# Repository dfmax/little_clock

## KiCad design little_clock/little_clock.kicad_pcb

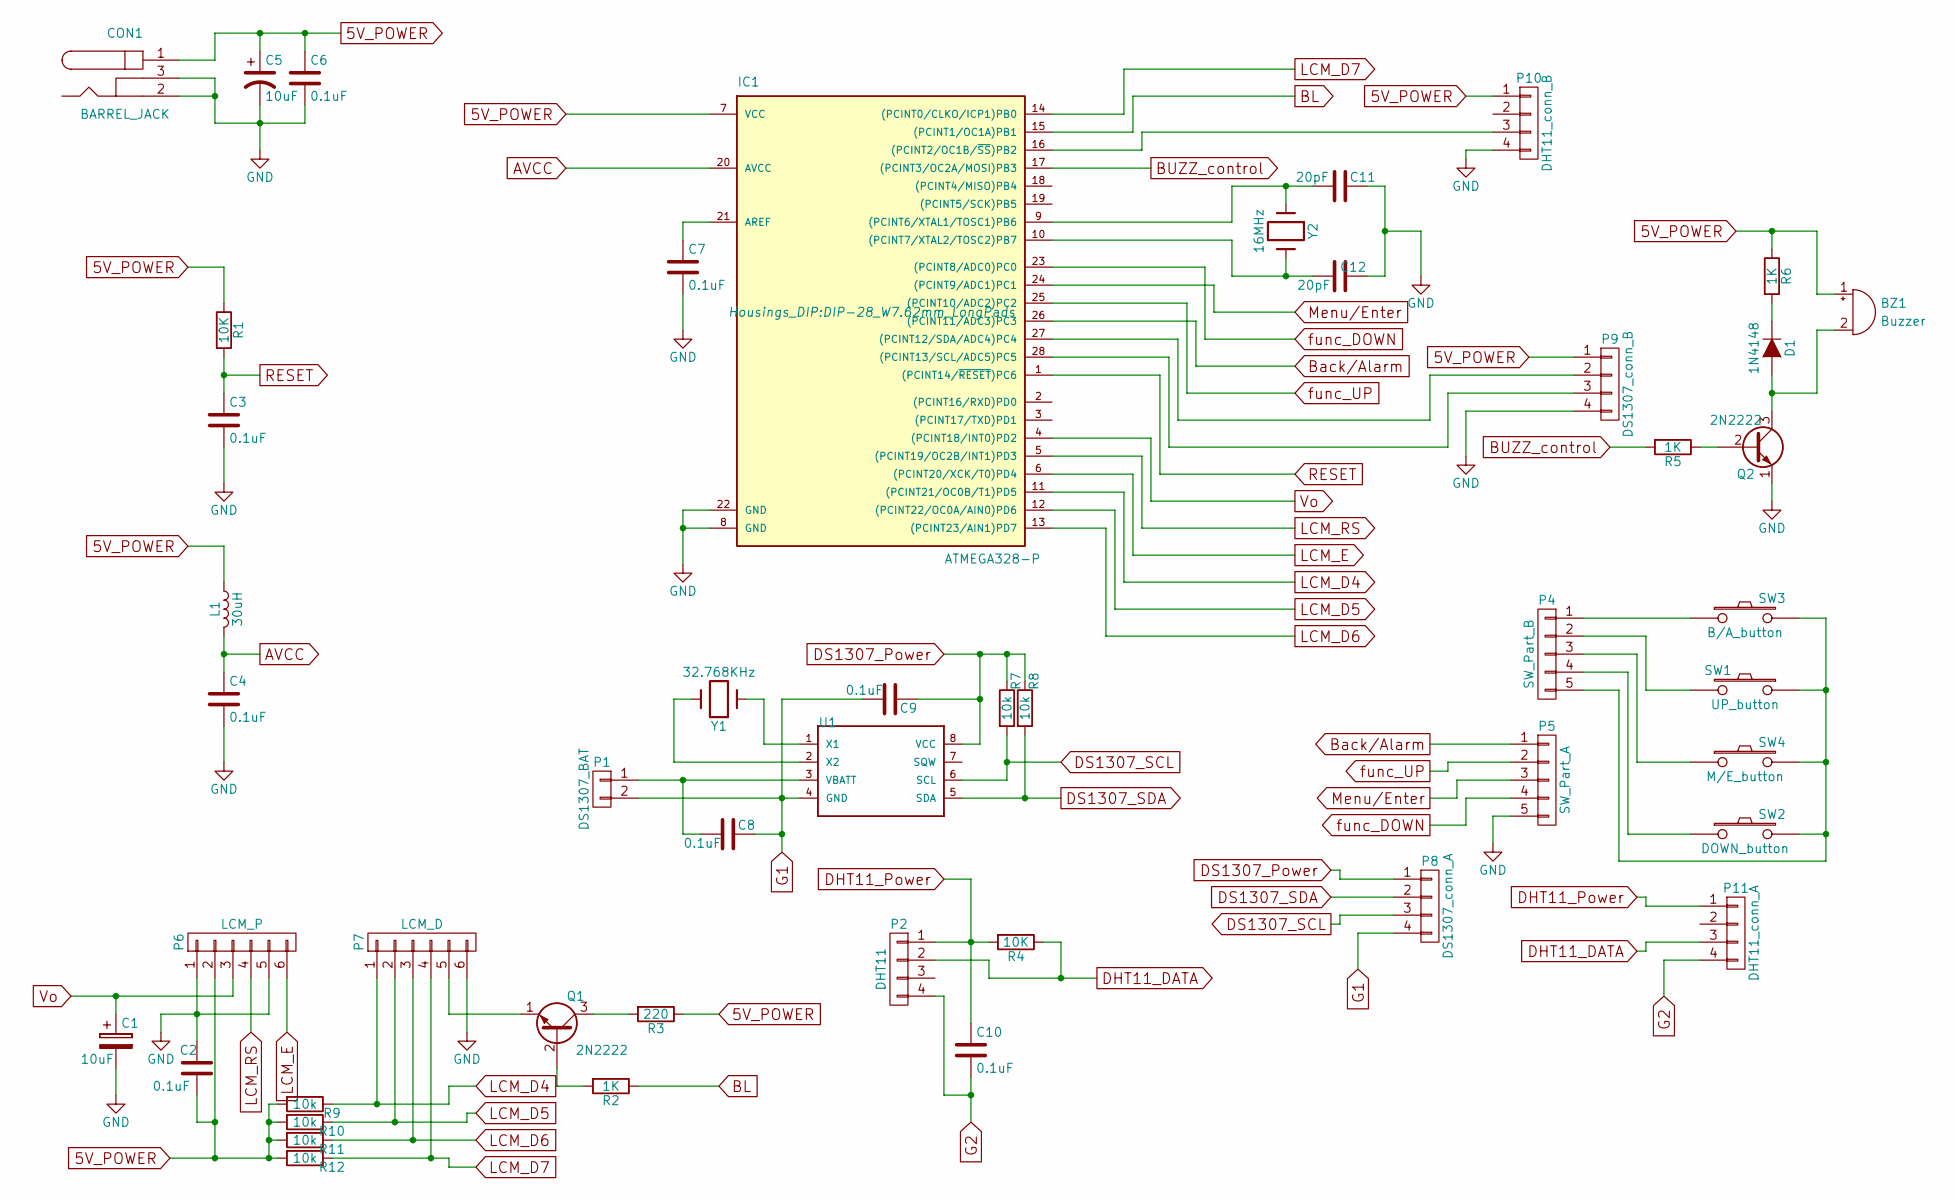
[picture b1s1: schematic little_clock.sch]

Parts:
BZ1: Buzzer; Buzzer_12x9.5RM7.6
C1, C5: 10uF; CP_Radial_D5.0mm_P2.50mm
C2, C6, C7, C8, C9, C10: 0.1uF; C_Disc_D5.0mm_W2.5mm_P5.00mm
C3, C4: 0.1uF; C_Disc_D4.7mm_W2.5mm_P5.00mm
C11, C12: 20pF; C_Disc_D3.0mm_W1.6mm_P2.50mm
CON1: BARREL_JACK
D1: 1N4148; D_DO-41_SOD81_P7.62mm_Horizontal
IC1: ATMEGA328-P; DIP-28_W7.62mm_LongPads
L1: 30uH; R_Axial_DIN0207_L6.3mm_D2.5mm_P10.16mm_Horizontal
P1: DS1307_BAT; Socket_Strip_Straight_2x01_Pitch2.54mm
P2: DHT11; Molex_NanoFit_1x04x2.50mm_Angled
P4: SW_Part_B; Pin_Header_Straight_1x05_Pitch2.54mm
P5: SW_Part_A; Pin_Header_Straight_1x05_Pitch2.54mm
P6: LCM_P; Pin_Header_Straight_1x06_Pitch2.54mm
P7: LCM_D; Pin_Header_Straight_1x06_Pitch2.54mm
P8: DS1307_conn_A; Pin_Header_Straight_1x04_Pitch2.54mm
P9: DS1307_conn_B; Pin_Header_Straight_1x04_Pitch2.54mm
P10: DHT11_conn_B; Pin_Header_Straight_1x04_Pitch2.54mm
P11: DHT11_conn_A; Pin_Header_Straight_1x04_Pitch2.54mm
Q1, Q2: 2N2222; TO-92_Inline_Wide
R1, R4: 10K; R_Axial_DIN0207_L6.3mm_D2.5mm_P10.16mm_Horizontal
R2, R5, R6: 1K; R_Axial_DIN0207_L6.3mm_D2.5mm_P10.16mm_Horizontal
R3: 220; R_Axial_DIN0207_L6.3mm_D2.5mm_P10.16mm_Horizontal
R7, R8, R9, R10, R11, R12: 10k; R_Axial_DIN0207_L6.3mm_D2.5mm_P10.16mm_Horizontal
SW1: UP_button; SW_PUSH_SMALL
SW2: DOWN_button; SW_PUSH_SMALL
SW3: B/A_button; SW_PUSH_SMALL
SW4: M/E_button; SW_PUSH_SMALL
U1: DS1307; DIP-8_W7.62mm_Socket_LongPads
Y1: 32.768KHz; Crystal_AT310_d3.0mm_l10.0mm_Horizontal
Y2: 16MHz; Crystal_HC18-U_Vertical

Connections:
5V_POWER: BZ1.1 (-), C2.2, C5.1, C6.1, CON1.1, IC1.7 (VCC), L1.1, P6.2, P9.1, P10.1, R1.1, R3.1, R6.1, R9.2, R10.2, R11.2, R12.2
AVCC: C4.1, IC1.20 (AVCC), L1.2
BL: IC1.15 ((PCINT1/OC1A)PB1), R2.1
BUZZ_control: IC1.17 ((PCINT3/OC2A/MOSI)PB3), R5.2
Back/Alarm: IC1.26 ((PCINT11/ADC3)PC3), P5.1
DHT11_DATA: P2.2, P11.3, R4.1
DHT11_Power: C10.1, P2.1, P11.1, R4.2
DS1307_Power: C9.1, P8.1, R7.1, R8.1, U1.8 (VCC)
DS1307_SCL: P8.3, R7.2, U1.6 (SCL)
DS1307_SDA: P8.2, R8.2, U1.5 (SDA)
G1: C8.1, C9.2, P1.2, P8.4, U1.4 (GND)
G2: C10.2, P2.4, P11.4
GND: C1.2, C2.1, C3.2, C4.2, C5.2, C6.2, C7.2, C11.1, C12.2, CON1.2, CON1.3, IC1.8 (GND), IC1.22 (GND), P5.5, P6.1, P6.5, P7.6, P9.4, P10.4, Q2.1 (E)
LCM_D4: IC1.11 ((PCINT21/OC0B/T1)PD5), P7.1, R9.1
LCM_D5: IC1.12 ((PCINT22/OC0A/AIN0)PD6), P7.2, R10.1
LCM_D6: IC1.13 ((PCINT23/AIN1)PD7), P7.3, R11.1
LCM_D7: IC1.14 ((PCINT0/CLKO/ICP1)PB0), P7.4, R12.1
LCM_E: IC1.6 ((PCINT20/XCK/T0)PD4), P6.6
LCM_RS: IC1.5 ((PCINT19/OC2B/INT1)PD3), P6.4
Menu/Enter: IC1.24 ((PCINT9/ADC1)PC1), P5.3
unnamed: BZ1.2 (+), D1.2 (A), Q2.3 (C)
unnamed: C7.1, IC1.21 (AREF)
unnamed: C8.2, P1.1, U1.3 (VBATT)
unnamed: C11.2, IC1.9 ((PCINT6/XTAL1/TOSC1)PB6), Y2.1
unnamed: C12.1, IC1.10 ((PCINT7/XTAL2/TOSC2)PB7), Y2.2
unnamed: D1.1 (K), R6.2
unnamed: IC1.16 ((PCINT2/OC1B/~SS~)PB2), P10.3
unnamed: IC1.27 ((PCINT12/SDA/ADC4)PC4), P9.2
unnamed: IC1.28 ((PCINT13/SCL/ADC5)PC5), P9.3
unnamed: P4.1, SW3.1
unnamed: P4.2, SW1.2
unnamed: P4.3, SW4.1
unnamed: P4.4, SW2.1
unnamed: P4.5, SW1.1, SW2.2, SW3.2, SW4.2
unnamed: P7.5, Q1.1 (E)
unnamed: Q1.2 (B), R2.2
unnamed: Q1.3 (C), R3.2
unnamed: Q2.2 (B), R5.1
unnamed: U1.1 (X1), Y1.1
unnamed: U1.2 (X2), Y1.2
RESET: C3.1, IC1.1 ((PCINT14/~RESET~)PC6), R1.2
Vo: C1.1, IC1.4 ((PCINT18/INT0)PD2), P6.3
func_DOWN: IC1.23 ((PCINT8/ADC0)PC0), P5.4
func_UP: IC1.25 ((PCINT10/ADC2)PC2), P5.2

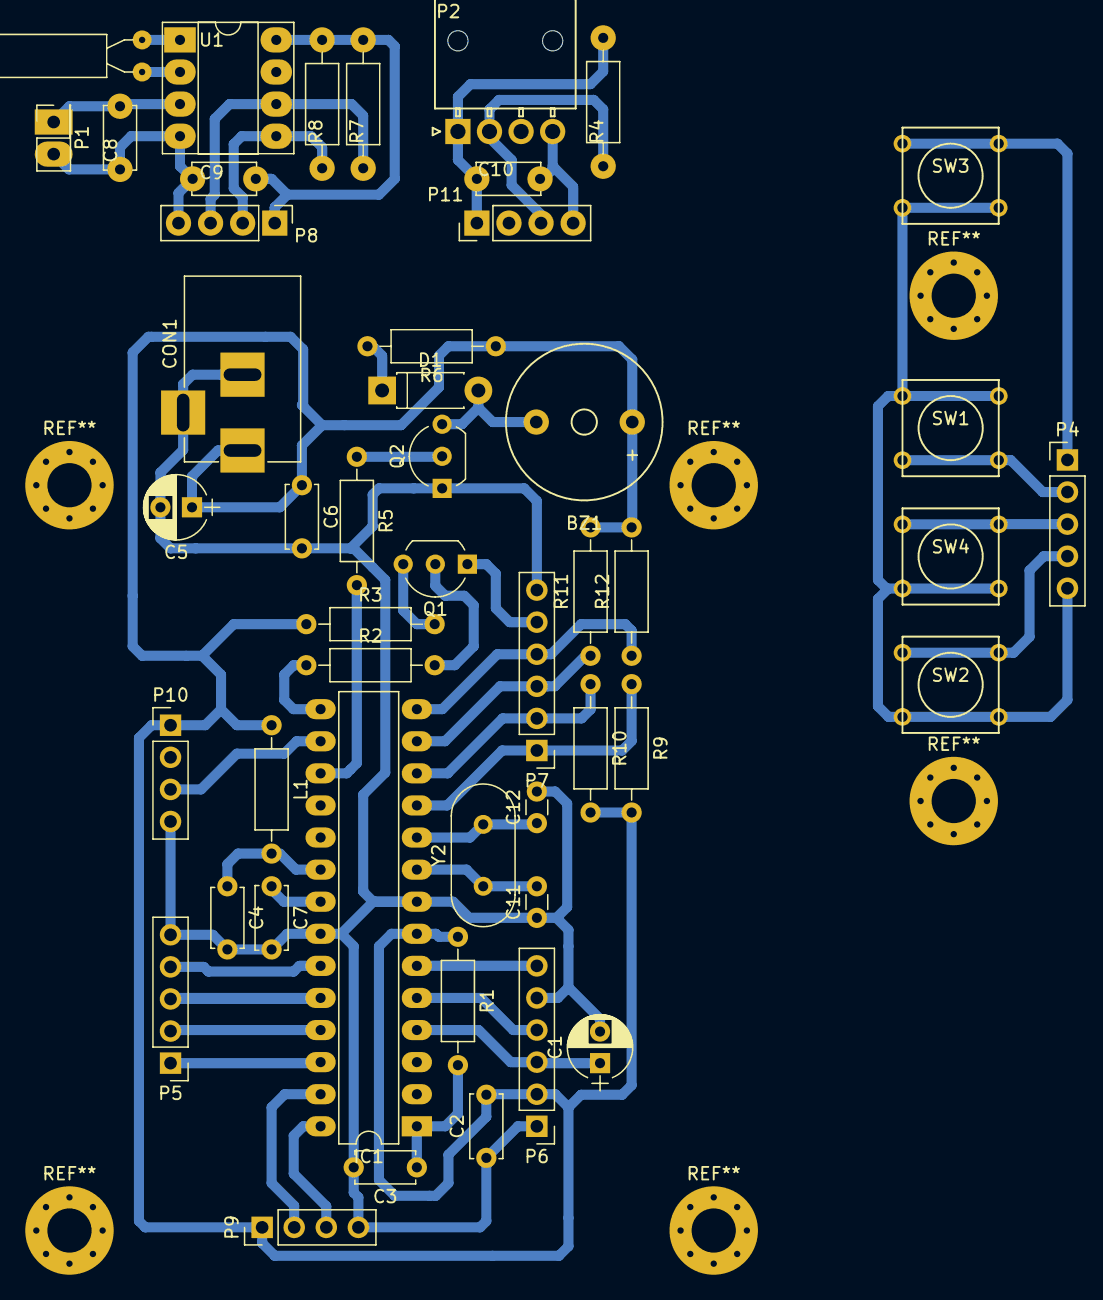
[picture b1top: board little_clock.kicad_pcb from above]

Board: 2 copper layers, 48 parts (0 on the bottom side), 44 nets.

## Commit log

2017-01-17 Basic functions for arduino digital clock
    functions by now:
    1. show time、date、temperature.
    2. autosave RTC time to eeprom.
    3. read RTC time.
    4. can using process code to control backlight and contrast.
2017-01-18 add some define, and fix initial display bug.
    add:
    1. add read LM35 data limit function.
    2. define control SW.
    3. setting show temperature limit to 99 degrees Celsius.
    edit:
    1. edit LM35 read delay time.
2017-01-19 add setting functions and LCM initial procedure.
    add:
    1. add go back functions Switch.
    2. add setting menu.
    3. add setFunction SW functions.
    4. add goBack SW functions.
    5. add initial LCM functions.
2017-01-20 add setUp and setDown part functions.
    add:
    1. add menu cursor refresh function.
    2. add setUp and setDown functions.
2017-01-21 change project position,and fix setting functions.
    change:
    1. Project content.
    2. setting menu display type.
    fix:
    1. fix goback SW not active bug.
    add:
2017-01-22 add setting time display item.
    add:
    1. show setting time item.
2017-01-23 add setting time functions.
    add:
    1. add setting and auto-save time(hour&minute).
    2. add go back to main menu functions.
2017-01-24 add setting Date functions, and fix EEPROM sccess so much times.
    add:
    1. setting Date.
    remove:
    1. Time data don't save to EEPROM.
    Bug:
    1. Year and Date ITEM are read error with EEPROM.
2017-02-02 add LCM setting functions define.
    ADD:
    1. add LCM backlight data with define.
    2. add LCM contrast data with define.
2017-02-02 fix Date setting bug.
    FIX:
    1. fix show wrong year bug.
    2. fix show wrong month bug.
2017-02-03 add LCM setting function, and fix some little bug.
    ADD:
    1. Add setting and auto-save LCM contrast.
    2. Add setting and auto-save LCM backlight.
    fix:
    1. fix some snippet code.
2017-02-04 add alarm functions and fix setting time bug.
    Add:
    1. alarm functions.
    2. add buzzer device.
    fix:
    1. fix setting DS1307 date bug.
2017-02-05 little_clock circuit design
    using KICAD to design arduino little_clock project.
2017-02-06 little_clock sch Ver.1.0
    little_clock sch Ver.1.0
2017-02-06 Little_clcok SCH Ver.1.0
    Little_clcok SCH Ver.1.0
2017-02-07 Little_clcok SCH Ver.1.0
    Little_clcok SCH Ver.1.0
2017-02-07 fix github
    fix github
2017-02-08 design Ver1.2
    design Ver1.2
2017-02-12 PCB Design Ver.1.0Beta
    PCB Design Ver.1.0Beta
2017-02-13 PCB Design V1.2
    PCB Design V1.2
2017-02-13 draw module
    draw clock module.
2017-02-13 PCB board pdf file.
    PCB board pdf file.
2017-02-18 3D Module recover file.
    3D Module recover file.
2017-02-18 3D module V1.2
    3D module V1.2
2017-02-19 create STL file for 3D printer.
    create:
    Top module
2017-02-19 checke module.
    checke module.
2017-03-04 update 3D module
    update 3D module
2017-03-04 stl diles for 3D printing
    buttom module.
2017-03-04 buttom module
    buttom module
